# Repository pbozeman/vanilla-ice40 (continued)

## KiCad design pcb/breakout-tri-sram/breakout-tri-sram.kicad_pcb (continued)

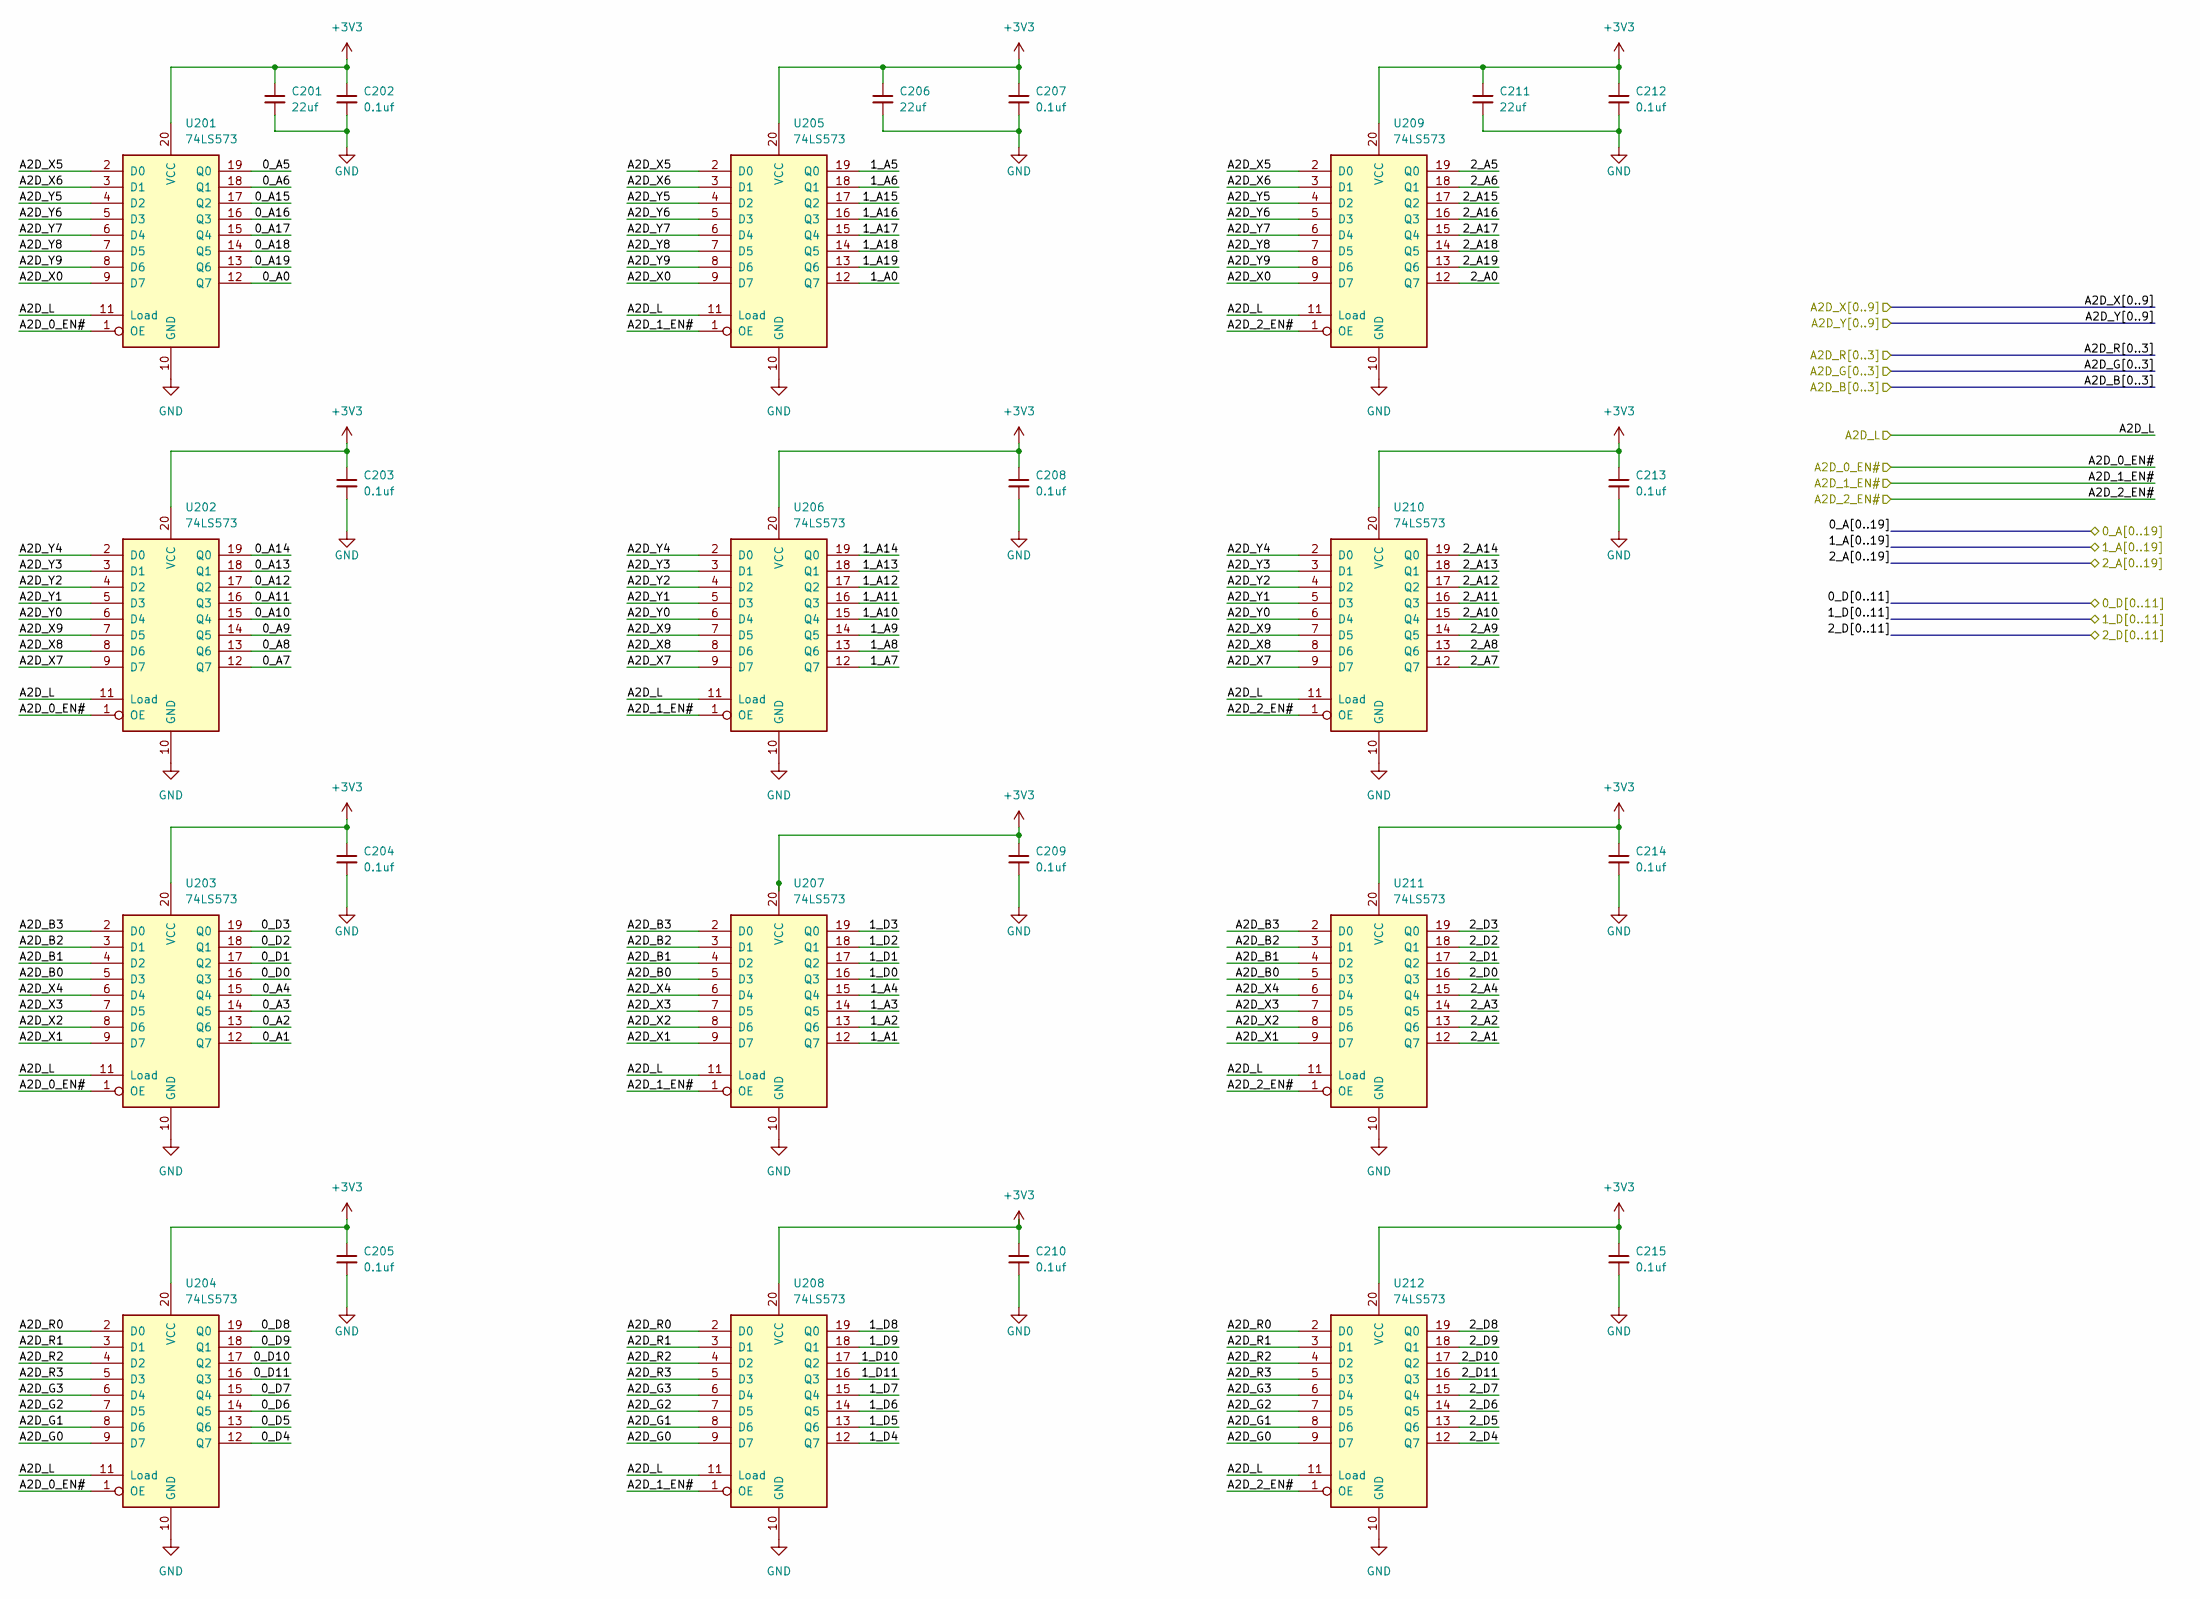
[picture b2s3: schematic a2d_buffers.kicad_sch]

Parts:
C201, C206, C211: 22uf; C_0603_1608Metric; LCSC Part # C59461
C202, C203, C204, C205, C207, C208, C209, C210, C212, C213, C214, C215: 0.1uf; C_0402_1005Metric; LCSC Part # C1525
U201, U202, U203, U204, U205, U206, U207, U208, U209, U210, U211, U212: 74LS573; SSOP-20_4.4x6.5mm_P0.65mm; LCSC Part # C7194124

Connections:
+3V3: C201.1, C202.1, C203.1, C204.1, C205.1, C206.1, C207.1, C208.1, C209.1, C210.1, C211.1, C212.1, C213.1, C214.1, C215.1, U201.20 (VCC), U202.20 (VCC), U203.20 (VCC), U204.20 (VCC), U205.20 (VCC), U206.20 (VCC), U207.20 (VCC), U208.20 (VCC), U209.20 (VCC), U210.20 (VCC), U211.20 (VCC), U212.20 (VCC); also elsewhere on the board
/0_A0: U201.12 (Q7); also elsewhere on the board
/0_A1: U203.12 (Q7); also elsewhere on the board
/0_A2: U203.13 (Q6); also elsewhere on the board
/0_A3: U203.14 (Q5); also elsewhere on the board
/0_A4: U203.15 (Q4); also elsewhere on the board
/0_A5: U201.19 (Q0); also elsewhere on the board
/0_A6: U201.18 (Q1); also elsewhere on the board
/0_A7: U202.12 (Q7); also elsewhere on the board
/0_A8: U202.13 (Q6); also elsewhere on the board
/0_A9: U202.14 (Q5); also elsewhere on the board
/0_A10: U202.15 (Q4); also elsewhere on the board
/0_A11: U202.16 (Q3); also elsewhere on the board
/0_A12: U202.17 (Q2); also elsewhere on the board
/0_A13: U202.18 (Q1); also elsewhere on the board
/0_A14: U202.19 (Q0); also elsewhere on the board
/0_A15: U201.17 (Q2); also elsewhere on the board
/0_A16: U201.16 (Q3); also elsewhere on the board
/0_A17: U201.15 (Q4); also elsewhere on the board
/0_A18: U201.14 (Q5); also elsewhere on the board
/0_A19: U201.13 (Q6); also elsewhere on the board
/0_D0: U203.16 (Q3); also elsewhere on the board
/0_D1: U203.17 (Q2); also elsewhere on the board
/0_D2: U203.18 (Q1); also elsewhere on the board
/0_D3: U203.19 (Q0); also elsewhere on the board
/0_D4: U204.12 (Q7); also elsewhere on the board
/0_D5: U204.13 (Q6); also elsewhere on the board
/0_D6: U204.14 (Q5); also elsewhere on the board
/0_D7: U204.15 (Q4); also elsewhere on the board
/0_D8: U204.19 (Q0); also elsewhere on the board
/0_D9: U204.18 (Q1); also elsewhere on the board
/0_D10: U204.17 (Q2); also elsewhere on the board
/0_D11: U204.16 (Q3); also elsewhere on the board
/1_A0: U205.12 (Q7); also elsewhere on the board
/1_A1: U207.12 (Q7); also elsewhere on the board
/1_A2: U207.13 (Q6); also elsewhere on the board
/1_A3: U207.14 (Q5); also elsewhere on the board
/1_A4: U207.15 (Q4); also elsewhere on the board
/1_A5: U205.19 (Q0); also elsewhere on the board
/1_A6: U205.18 (Q1); also elsewhere on the board
/1_A7: U206.12 (Q7); also elsewhere on the board
/1_A8: U206.13 (Q6); also elsewhere on the board
/1_A9: U206.14 (Q5); also elsewhere on the board
/1_A10: U206.15 (Q4); also elsewhere on the board
/1_A11: U206.16 (Q3); also elsewhere on the board
/1_A12: U206.17 (Q2); also elsewhere on the board
/1_A13: U206.18 (Q1); also elsewhere on the board
/1_A14: U206.19 (Q0); also elsewhere on the board
/1_A15: U205.17 (Q2); also elsewhere on the board
/1_A16: U205.16 (Q3); also elsewhere on the board
/1_A17: U205.15 (Q4); also elsewhere on the board
/1_A18: U205.14 (Q5); also elsewhere on the board
/1_A19: U205.13 (Q6); also elsewhere on the board
/1_D0: U207.16 (Q3); also elsewhere on the board
/1_D1: U207.17 (Q2); also elsewhere on the board
/1_D2: U207.18 (Q1); also elsewhere on the board
/1_D3: U207.19 (Q0); also elsewhere on the board
/1_D4: U208.12 (Q7); also elsewhere on the board
/1_D5: U208.13 (Q6); also elsewhere on the board
/1_D6: U208.14 (Q5); also elsewhere on the board
/1_D7: U208.15 (Q4); also elsewhere on the board
/1_D8: U208.19 (Q0); also elsewhere on the board
/1_D9: U208.18 (Q1); also elsewhere on the board
/1_D10: U208.17 (Q2); also elsewhere on the board
/1_D11: U208.16 (Q3); also elsewhere on the board
/2_A0: U209.12 (Q7); also elsewhere on the board
/2_A1: U211.12 (Q7); also elsewhere on the board
/2_A2: U211.13 (Q6); also elsewhere on the board
/2_A3: U211.14 (Q5); also elsewhere on the board
/2_A4: U211.15 (Q4); also elsewhere on the board
/2_A5: U209.19 (Q0); also elsewhere on the board
/2_A6: U209.18 (Q1); also elsewhere on the board
/2_A7: U210.12 (Q7); also elsewhere on the board
/2_A8: U210.13 (Q6); also elsewhere on the board
/2_A9: U210.14 (Q5); also elsewhere on the board
/2_A10: U210.15 (Q4); also elsewhere on the board
/2_A11: U210.16 (Q3); also elsewhere on the board
/2_A12: U210.17 (Q2); also elsewhere on the board
/2_A13: U210.18 (Q1); also elsewhere on the board
/2_A14: U210.19 (Q0); also elsewhere on the board
/2_A15: U209.17 (Q2); also elsewhere on the board
/2_A16: U209.16 (Q3); also elsewhere on the board
/2_A17: U209.15 (Q4); also elsewhere on the board
/2_A18: U209.14 (Q5); also elsewhere on the board
/2_A19: U209.13 (Q6); also elsewhere on the board
/2_D0: U211.16 (Q3); also elsewhere on the board
/2_D1: U211.17 (Q2); also elsewhere on the board
/2_D2: U211.18 (Q1); also elsewhere on the board
/2_D3: U211.19 (Q0); also elsewhere on the board
/2_D4: U212.12 (Q7); also elsewhere on the board
/2_D5: U212.13 (Q6); also elsewhere on the board
/2_D6: U212.14 (Q5); also elsewhere on the board
/2_D7: U212.15 (Q4); also elsewhere on the board
/2_D8: U212.19 (Q0); also elsewhere on the board
/2_D9: U212.18 (Q1); also elsewhere on the board
/2_D10: U212.17 (Q2); also elsewhere on the board
/2_D11: U212.16 (Q3); also elsewhere on the board
/A2D_0_EN#: U201.1 (OE), U202.1 (OE), U203.1 (OE), U204.1 (OE); also elsewhere on the board
/A2D_1_EN#: U205.1 (OE), U206.1 (OE), U207.1 (OE), U208.1 (OE); also elsewhere on the board
/A2D_2_EN#: U209.1 (OE), U210.1 (OE), U211.1 (OE), U212.1 (OE); also elsewhere on the board
/A2D_B0: U203.5 (D3), U207.5 (D3), U211.5 (D3); also elsewhere on the board
/A2D_B1: U203.4 (D2), U207.4 (D2), U211.4 (D2); also elsewhere on the board
/A2D_B2: U203.3 (D1), U207.3 (D1), U211.3 (D1); also elsewhere on the board
/A2D_B3: U203.2 (D0), U207.2 (D0), U211.2 (D0); also elsewhere on the board
/A2D_G0: U204.9 (D7), U208.9 (D7), U212.9 (D7); also elsewhere on the board
/A2D_G1: U204.8 (D6), U208.8 (D6), U212.8 (D6); also elsewhere on the board
/A2D_G2: U204.7 (D5), U208.7 (D5), U212.7 (D5); also elsewhere on the board
/A2D_G3: U204.6 (D4), U208.6 (D4), U212.6 (D4); also elsewhere on the board
/A2D_L: U201.11 (Load), U202.11 (Load), U203.11 (Load), U204.11 (Load), U205.11 (Load), U206.11 (Load), U207.11 (Load), U208.11 (Load), U209.11 (Load), U210.11 (Load), U211.11 (Load), U212.11 (Load); also elsewhere on the board
/A2D_R0: U204.2 (D0), U208.2 (D0), U212.2 (D0); also elsewhere on the board
/A2D_R1: U204.3 (D1), U208.3 (D1), U212.3 (D1); also elsewhere on the board
/A2D_R2: U204.4 (D2), U208.4 (D2), U212.4 (D2); also elsewhere on the board
/A2D_R3: U204.5 (D3), U208.5 (D3), U212.5 (D3); also elsewhere on the board
/A2D_X0: U201.9 (D7), U205.9 (D7), U209.9 (D7); also elsewhere on the board
/A2D_X1: U203.9 (D7), U207.9 (D7), U211.9 (D7); also elsewhere on the board
/A2D_X2: U203.8 (D6), U207.8 (D6), U211.8 (D6); also elsewhere on the board
/A2D_X3: U203.7 (D5), U207.7 (D5), U211.7 (D5); also elsewhere on the board
/A2D_X4: U203.6 (D4), U207.6 (D4), U211.6 (D4); also elsewhere on the board
/A2D_X5: U201.2 (D0), U205.2 (D0), U209.2 (D0); also elsewhere on the board
/A2D_X6: U201.3 (D1), U205.3 (D1), U209.3 (D1); also elsewhere on the board
/A2D_X7: U202.9 (D7), U206.9 (D7), U210.9 (D7); also elsewhere on the board
/A2D_X8: U202.8 (D6), U206.8 (D6), U210.8 (D6); also elsewhere on the board
/A2D_X9: U202.7 (D5), U206.7 (D5), U210.7 (D5); also elsewhere on the board
/A2D_Y0: U202.6 (D4), U206.6 (D4), U210.6 (D4); also elsewhere on the board
/A2D_Y1: U202.5 (D3), U206.5 (D3), U210.5 (D3); also elsewhere on the board
/A2D_Y2: U202.4 (D2), U206.4 (D2), U210.4 (D2); also elsewhere on the board
/A2D_Y3: U202.3 (D1), U206.3 (D1), U210.3 (D1); also elsewhere on the board
/A2D_Y4: U202.2 (D0), U206.2 (D0), U210.2 (D0); also elsewhere on the board
/A2D_Y5: U201.4 (D2), U205.4 (D2), U209.4 (D2); also elsewhere on the board
/A2D_Y6: U201.5 (D3), U205.5 (D3), U209.5 (D3); also elsewhere on the board
/A2D_Y7: U201.6 (D4), U205.6 (D4), U209.6 (D4); also elsewhere on the board
/A2D_Y8: U201.7 (D5), U205.7 (D5), U209.7 (D5); also elsewhere on the board
/A2D_Y9: U201.8 (D6), U205.8 (D6), U209.8 (D6); also elsewhere on the board
GND: C201.2, C202.2, C203.2, C204.2, C205.2, C206.2, C207.2, C208.2, C209.2, C210.2, C211.2, C212.2, C213.2, C214.2, C215.2, U201.10 (GND), U202.10 (GND), U203.10 (GND), U204.10 (GND), U205.10 (GND), U206.10 (GND), U207.10 (GND), U208.10 (GND), U209.10 (GND), U210.10 (GND), U211.10 (GND), U212.10 (GND); also elsewhere on the board

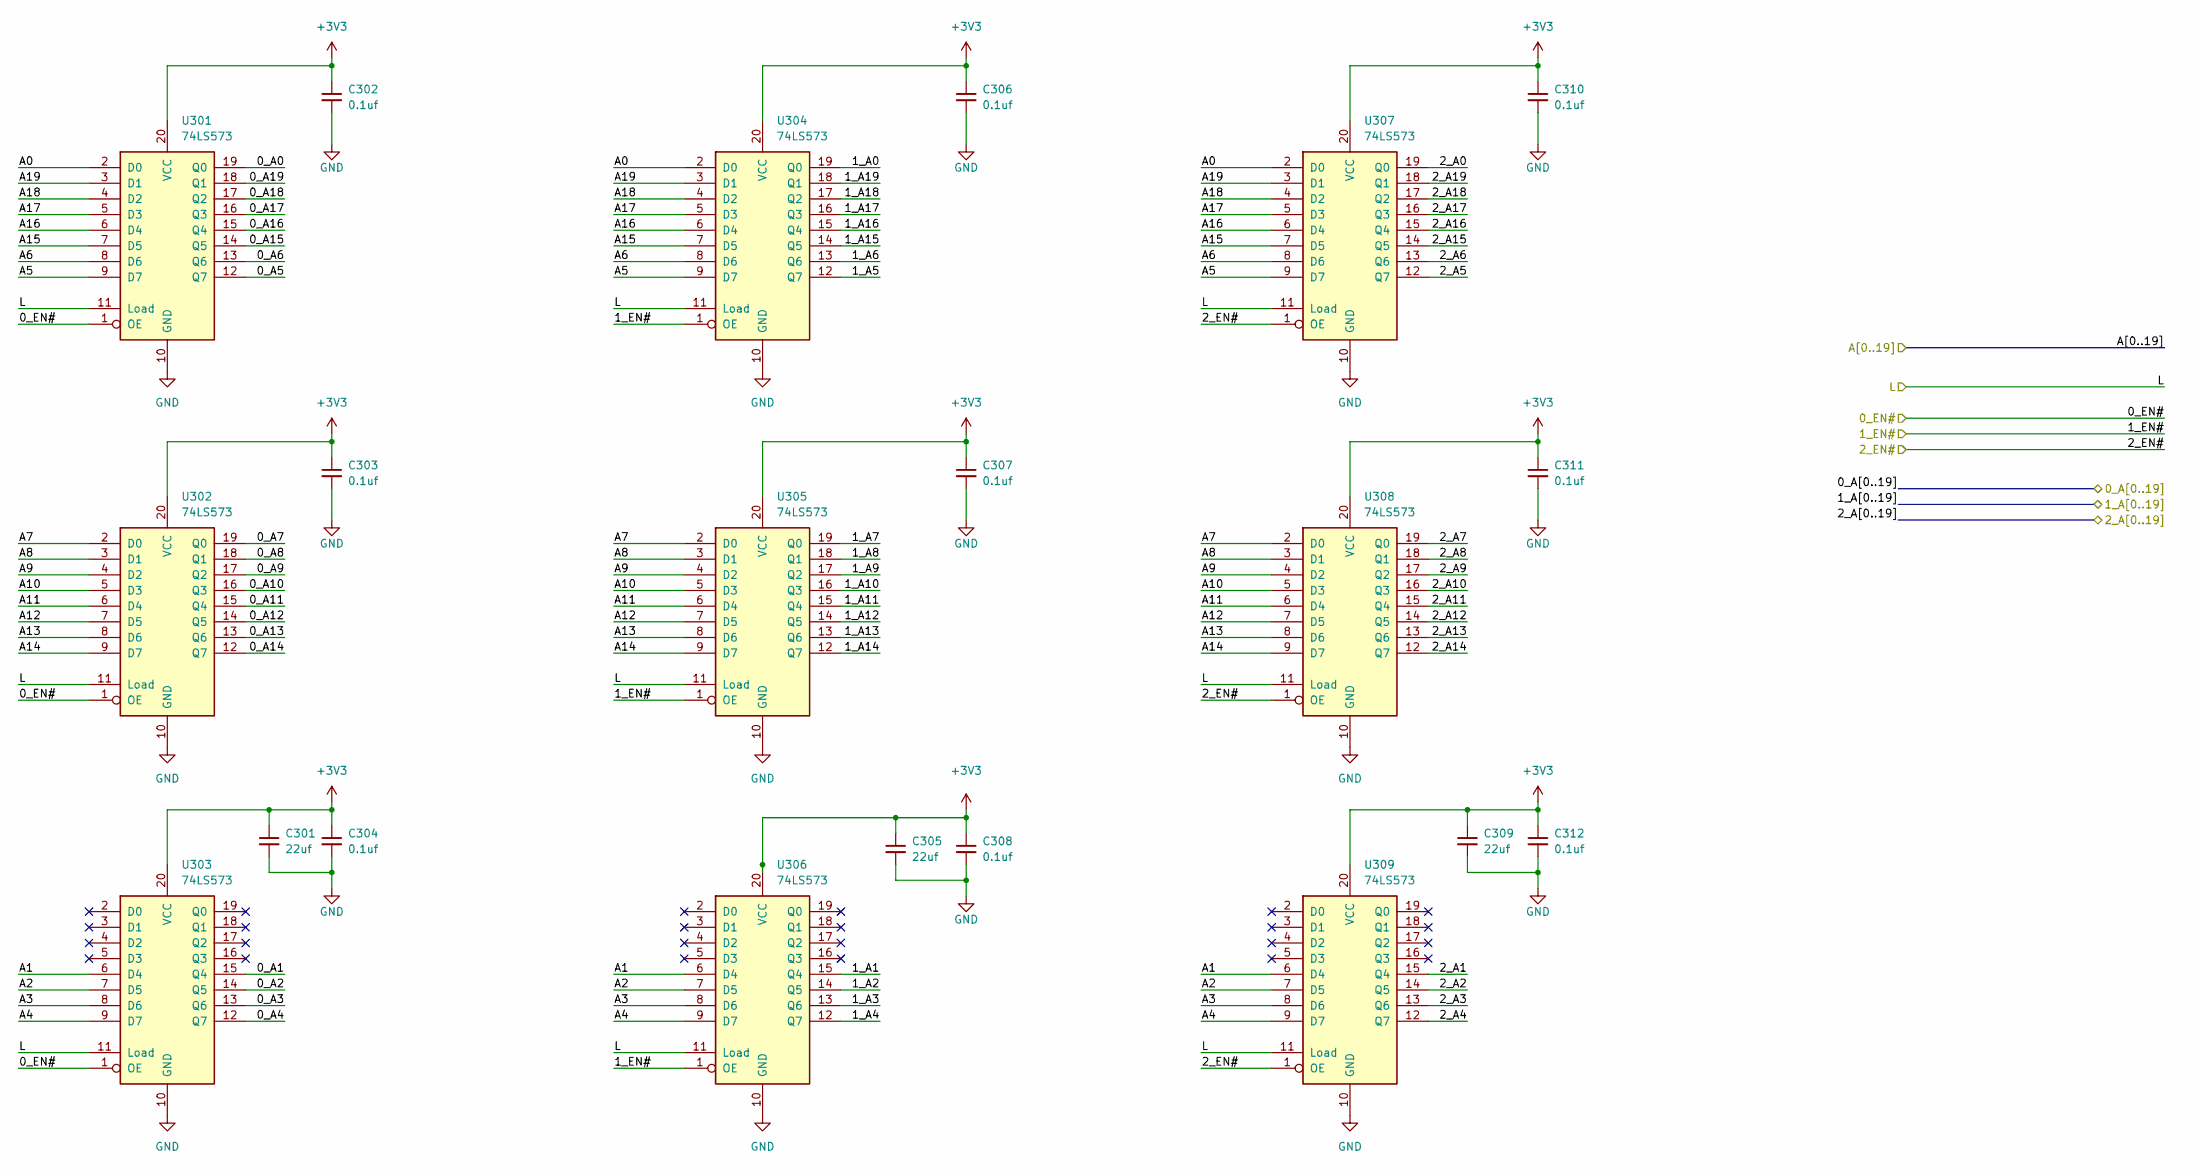
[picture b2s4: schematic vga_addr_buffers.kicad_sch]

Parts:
C301, C305, C309: 22uf; C_0603_1608Metric; LCSC Part # C59461
C302, C303, C304, C306, C307, C308, C310, C311, C312: 0.1uf; C_0402_1005Metric; LCSC Part # C1525
U301, U302, U303, U304, U305, U306, U307, U308, U309: 74LS573; SSOP-20_4.4x6.5mm_P0.65mm; LCSC Part # C7194124

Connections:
+3V3: C301.1, C302.1, C303.1, C304.1, C305.1, C306.1, C307.1, C308.1, C309.1, C310.1, C311.1, C312.1, U301.20 (VCC), U302.20 (VCC), U303.20 (VCC), U304.20 (VCC), U305.20 (VCC), U306.20 (VCC), U307.20 (VCC), U308.20 (VCC), U309.20 (VCC); also elsewhere on the board
/0_A0: U301.19 (Q0); also elsewhere on the board
/0_A1: U303.15 (Q4); also elsewhere on the board
/0_A2: U303.14 (Q5); also elsewhere on the board
/0_A3: U303.13 (Q6); also elsewhere on the board
/0_A4: U303.12 (Q7); also elsewhere on the board
/0_A5: U301.12 (Q7); also elsewhere on the board
/0_A6: U301.13 (Q6); also elsewhere on the board
/0_A7: U302.19 (Q0); also elsewhere on the board
/0_A8: U302.18 (Q1); also elsewhere on the board
/0_A9: U302.17 (Q2); also elsewhere on the board
/0_A10: U302.16 (Q3); also elsewhere on the board
/0_A11: U302.15 (Q4); also elsewhere on the board
/0_A12: U302.14 (Q5); also elsewhere on the board
/0_A13: U302.13 (Q6); also elsewhere on the board
/0_A14: U302.12 (Q7); also elsewhere on the board
/0_A15: U301.14 (Q5); also elsewhere on the board
/0_A16: U301.15 (Q4); also elsewhere on the board
/0_A17: U301.16 (Q3); also elsewhere on the board
/0_A18: U301.17 (Q2); also elsewhere on the board
/0_A19: U301.18 (Q1); also elsewhere on the board
/1_A0: U304.19 (Q0); also elsewhere on the board
/1_A1: U306.15 (Q4); also elsewhere on the board
/1_A2: U306.14 (Q5); also elsewhere on the board
/1_A3: U306.13 (Q6); also elsewhere on the board
/1_A4: U306.12 (Q7); also elsewhere on the board
/1_A5: U304.12 (Q7); also elsewhere on the board
/1_A6: U304.13 (Q6); also elsewhere on the board
/1_A7: U305.19 (Q0); also elsewhere on the board
/1_A8: U305.18 (Q1); also elsewhere on the board
/1_A9: U305.17 (Q2); also elsewhere on the board
/1_A10: U305.16 (Q3); also elsewhere on the board
/1_A11: U305.15 (Q4); also elsewhere on the board
/1_A12: U305.14 (Q5); also elsewhere on the board
/1_A13: U305.13 (Q6); also elsewhere on the board
/1_A14: U305.12 (Q7); also elsewhere on the board
/1_A15: U304.14 (Q5); also elsewhere on the board
/1_A16: U304.15 (Q4); also elsewhere on the board
/1_A17: U304.16 (Q3); also elsewhere on the board
/1_A18: U304.17 (Q2); also elsewhere on the board
/1_A19: U304.18 (Q1); also elsewhere on the board
/2_A0: U307.19 (Q0); also elsewhere on the board
/2_A1: U309.15 (Q4); also elsewhere on the board
/2_A2: U309.14 (Q5); also elsewhere on the board
/2_A3: U309.13 (Q6); also elsewhere on the board
/2_A4: U309.12 (Q7); also elsewhere on the board
/2_A5: U307.12 (Q7); also elsewhere on the board
/2_A6: U307.13 (Q6); also elsewhere on the board
/2_A7: U308.19 (Q0); also elsewhere on the board
/2_A8: U308.18 (Q1); also elsewhere on the board
/2_A9: U308.17 (Q2); also elsewhere on the board
/2_A10: U308.16 (Q3); also elsewhere on the board
/2_A11: U308.15 (Q4); also elsewhere on the board
/2_A12: U308.14 (Q5); also elsewhere on the board
/2_A13: U308.13 (Q6); also elsewhere on the board
/2_A14: U308.12 (Q7); also elsewhere on the board
/2_A15: U307.14 (Q5); also elsewhere on the board
/2_A16: U307.15 (Q4); also elsewhere on the board
/2_A17: U307.16 (Q3); also elsewhere on the board
/2_A18: U307.17 (Q2); also elsewhere on the board
/2_A19: U307.18 (Q1); also elsewhere on the board
/VGA_0_A_EN#: U301.1 (OE), U302.1 (OE), U303.1 (OE); also elsewhere on the board
/VGA_1_A_EN#: U304.1 (OE), U305.1 (OE), U306.1 (OE); also elsewhere on the board
/VGA_2_A_EN#: U307.1 (OE), U308.1 (OE), U309.1 (OE); also elsewhere on the board
/VGA_A0: U301.2 (D0), U304.2 (D0), U307.2 (D0); also elsewhere on the board
/VGA_A1: U303.6 (D4), U306.6 (D4), U309.6 (D4); also elsewhere on the board
/VGA_A2: U303.7 (D5), U306.7 (D5), U309.7 (D5); also elsewhere on the board
/VGA_A3: U303.8 (D6), U306.8 (D6), U309.8 (D6); also elsewhere on the board
/VGA_A4: U303.9 (D7), U306.9 (D7), U309.9 (D7); also elsewhere on the board
/VGA_A5: U301.9 (D7), U304.9 (D7), U307.9 (D7); also elsewhere on the board
/VGA_A6: U301.8 (D6), U304.8 (D6), U307.8 (D6); also elsewhere on the board
/VGA_A7: U302.2 (D0), U305.2 (D0), U308.2 (D0); also elsewhere on the board
/VGA_A8: U302.3 (D1), U305.3 (D1), U308.3 (D1); also elsewhere on the board
/VGA_A9: U302.4 (D2), U305.4 (D2), U308.4 (D2); also elsewhere on the board
/VGA_A10: U302.5 (D3), U305.5 (D3), U308.5 (D3); also elsewhere on the board
/VGA_A11: U302.6 (D4), U305.6 (D4), U308.6 (D4); also elsewhere on the board
/VGA_A12: U302.7 (D5), U305.7 (D5), U308.7 (D5); also elsewhere on the board
/VGA_A13: U302.8 (D6), U305.8 (D6), U308.8 (D6); also elsewhere on the board
/VGA_A14: U302.9 (D7), U305.9 (D7), U308.9 (D7); also elsewhere on the board
/VGA_A15: U301.7 (D5), U304.7 (D5), U307.7 (D5); also elsewhere on the board
/VGA_A16: U301.6 (D4), U304.6 (D4), U307.6 (D4); also elsewhere on the board
/VGA_A17: U301.5 (D3), U304.5 (D3), U307.5 (D3); also elsewhere on the board
/VGA_A18: U301.4 (D2), U304.4 (D2), U307.4 (D2); also elsewhere on the board
/VGA_A19: U301.3 (D1), U304.3 (D1), U307.3 (D1); also elsewhere on the board
/VGA_A_L: U301.11 (Load), U302.11 (Load), U303.11 (Load), U304.11 (Load), U305.11 (Load), U306.11 (Load), U307.11 (Load), U308.11 (Load), U309.11 (Load); also elsewhere on the board
GND: C301.2, C302.2, C303.2, C304.2, C305.2, C306.2, C307.2, C308.2, C309.2, C310.2, C311.2, C312.2, U301.10 (GND), U302.10 (GND), U303.10 (GND), U304.10 (GND), U305.10 (GND), U306.10 (GND), U307.10 (GND), U308.10 (GND), U309.10 (GND); also elsewhere on the board

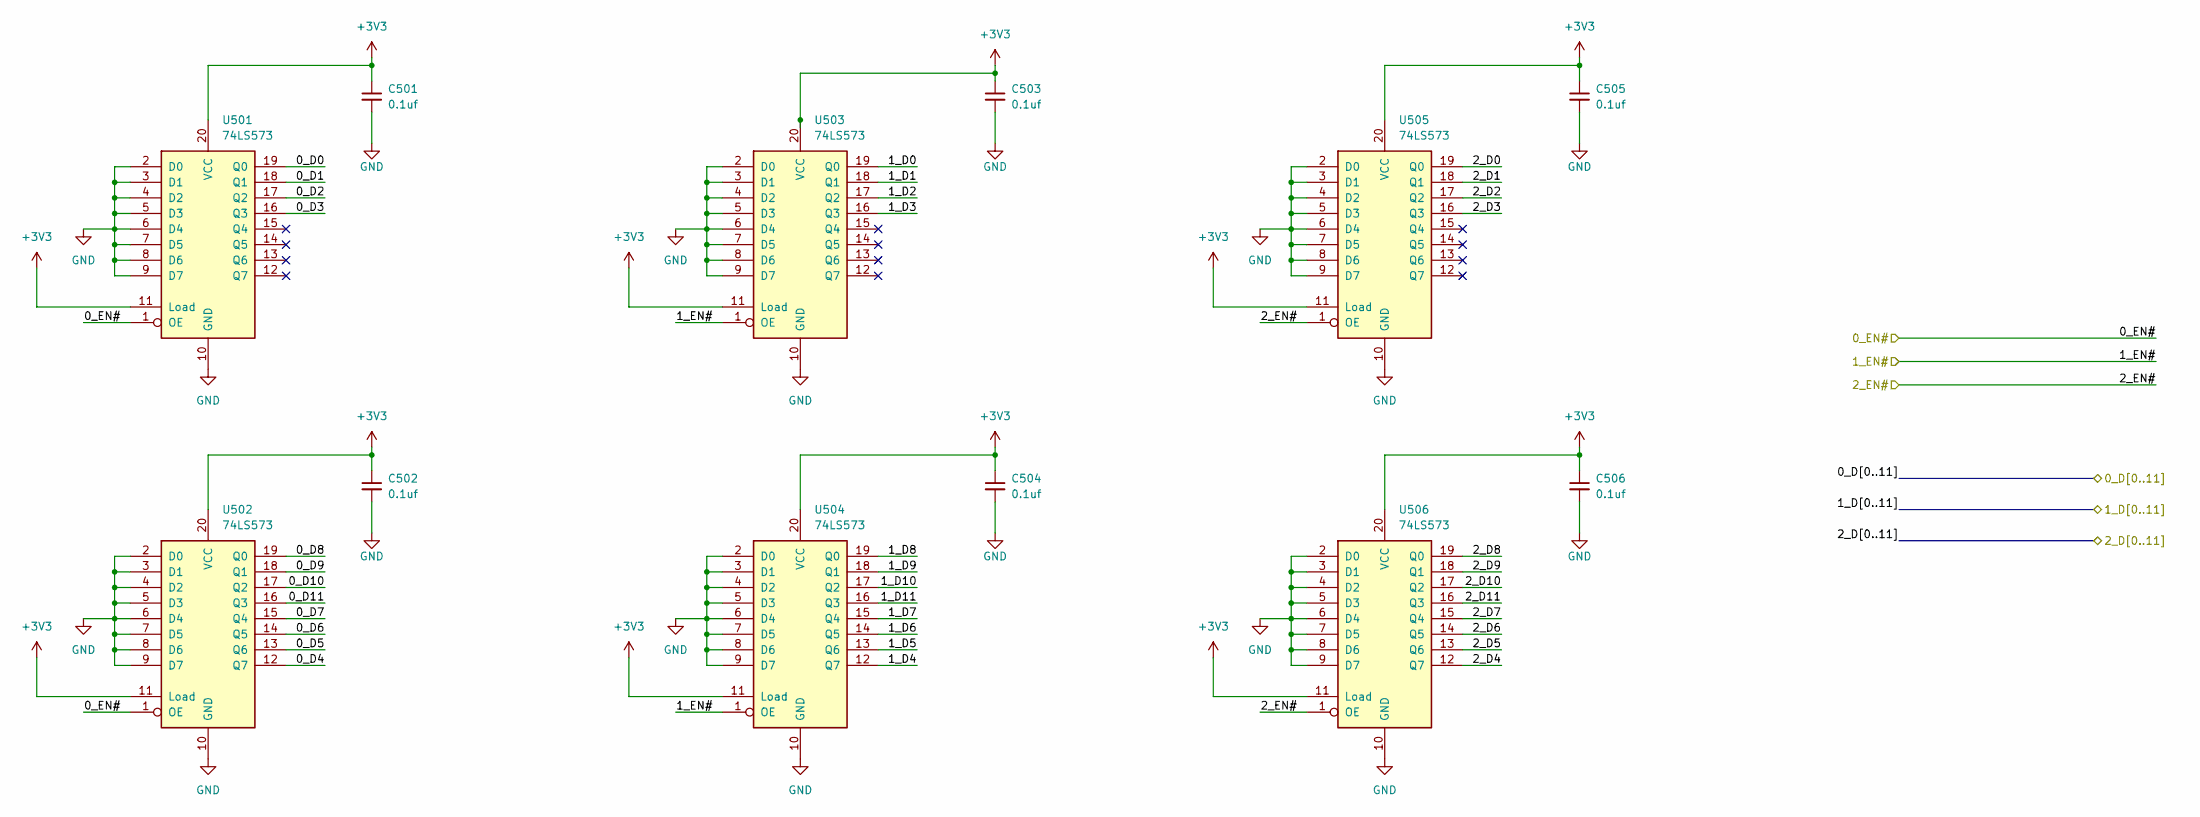
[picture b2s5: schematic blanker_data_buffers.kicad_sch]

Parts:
C501, C502, C503, C504, C505, C506: 0.1uf; C_0402_1005Metric; LCSC Part # C1525
U501, U502, U503, U504, U505, U506: 74LS573; SSOP-20_4.4x6.5mm_P0.65mm; LCSC Part # C7194124

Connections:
+3V3: C501.1, C502.1, C503.1, C504.1, C505.1, C506.1, U501.11 (Load), U501.20 (VCC), U502.11 (Load), U502.20 (VCC), U503.11 (Load), U503.20 (VCC), U504.11 (Load), U504.20 (VCC), U505.11 (Load), U505.20 (VCC), U506.11 (Load), U506.20 (VCC); also elsewhere on the board
/0_D0: U501.19 (Q0); also elsewhere on the board
/0_D1: U501.18 (Q1); also elsewhere on the board
/0_D2: U501.17 (Q2); also elsewhere on the board
/0_D3: U501.16 (Q3); also elsewhere on the board
/0_D4: U502.12 (Q7); also elsewhere on the board
/0_D5: U502.13 (Q6); also elsewhere on the board
/0_D6: U502.14 (Q5); also elsewhere on the board
/0_D7: U502.15 (Q4); also elsewhere on the board
/0_D8: U502.19 (Q0); also elsewhere on the board
/0_D9: U502.18 (Q1); also elsewhere on the board
/0_D10: U502.17 (Q2); also elsewhere on the board
/0_D11: U502.16 (Q3); also elsewhere on the board
/1_D0: U503.19 (Q0); also elsewhere on the board
/1_D1: U503.18 (Q1); also elsewhere on the board
/1_D2: U503.17 (Q2); also elsewhere on the board
/1_D3: U503.16 (Q3); also elsewhere on the board
/1_D4: U504.12 (Q7); also elsewhere on the board
/1_D5: U504.13 (Q6); also elsewhere on the board
/1_D6: U504.14 (Q5); also elsewhere on the board
/1_D7: U504.15 (Q4); also elsewhere on the board
/1_D8: U504.19 (Q0); also elsewhere on the board
/1_D9: U504.18 (Q1); also elsewhere on the board
/1_D10: U504.17 (Q2); also elsewhere on the board
/1_D11: U504.16 (Q3); also elsewhere on the board
/2_D0: U505.19 (Q0); also elsewhere on the board
/2_D1: U505.18 (Q1); also elsewhere on the board
/2_D2: U505.17 (Q2); also elsewhere on the board
/2_D3: U505.16 (Q3); also elsewhere on the board
/2_D4: U506.12 (Q7); also elsewhere on the board
/2_D5: U506.13 (Q6); also elsewhere on the board
/2_D6: U506.14 (Q5); also elsewhere on the board
/2_D7: U506.15 (Q4); also elsewhere on the board
/2_D8: U506.19 (Q0); also elsewhere on the board
/2_D9: U506.18 (Q1); also elsewhere on the board
/2_D10: U506.17 (Q2); also elsewhere on the board
/2_D11: U506.16 (Q3); also elsewhere on the board
/BLK_0_EN#: U501.1 (OE), U502.1 (OE); also elsewhere on the board
/BLK_1_EN#: U503.1 (OE), U504.1 (OE); also elsewhere on the board
/BLK_2_EN#: U505.1 (OE), U506.1 (OE); also elsewhere on the board
GND: C501.2, C502.2, C503.2, C504.2, C505.2, C506.2, U501.2 (D0), U501.3 (D1), U501.4 (D2), U501.5 (D3), U501.6 (D4), U501.7 (D5), U501.8 (D6), U501.9 (D7), U501.10 (GND), U502.2 (D0), U502.3 (D1), U502.4 (D2), U502.5 (D3), U502.6 (D4), U502.7 (D5), U502.8 (D6), U502.9 (D7), U502.10 (GND), U503.2 (D0), U503.3 (D1), U503.4 (D2), U503.5 (D3), U503.6 (D4), U503.7 (D5), U503.8 (D6), U503.9 (D7), U503.10 (GND), U504.2 (D0), U504.3 (D1), U504.4 (D2), U504.5 (D3), U504.6 (D4), U504.7 (D5), U504.8 (D6), U504.9 (D7), U504.10 (GND), U505.2 (D0), U505.3 (D1), U505.4 (D2), U505.5 (D3), U505.6 (D4), U505.7 (D5), U505.8 (D6), U505.9 (D7), U505.10 (GND), U506.2 (D0), U506.3 (D1), U506.4 (D2), U506.5 (D3), U506.6 (D4), U506.7 (D5), U506.8 (D6), U506.9 (D7), U506.10 (GND); also elsewhere on the board

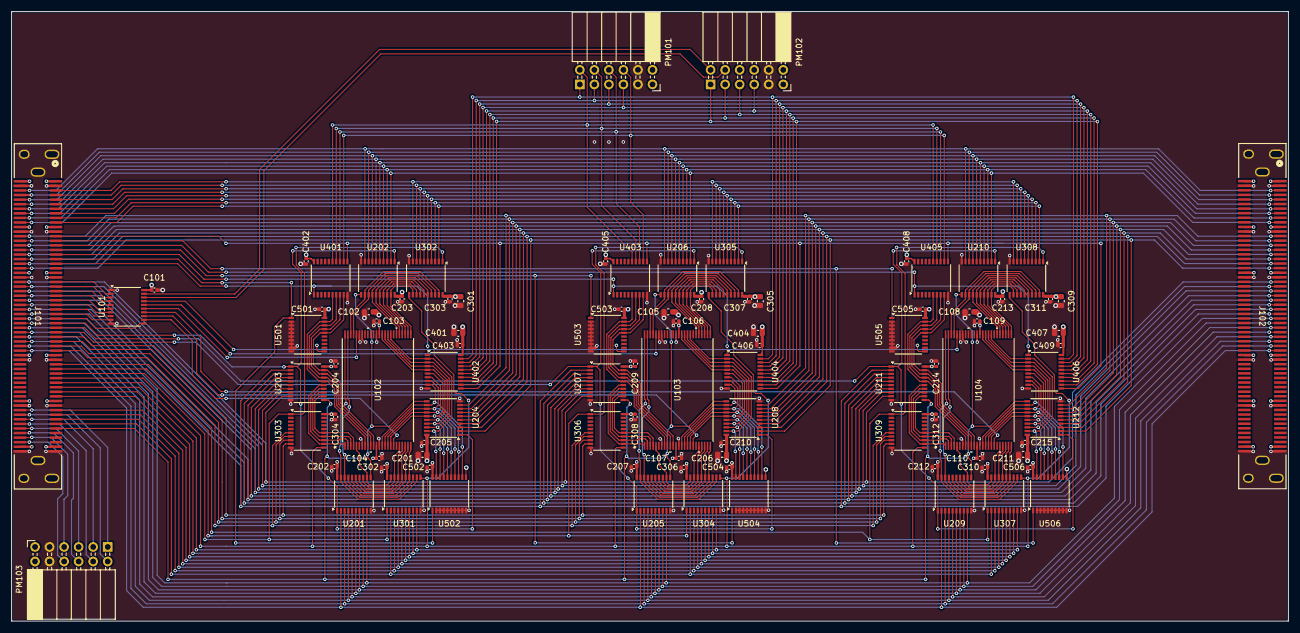
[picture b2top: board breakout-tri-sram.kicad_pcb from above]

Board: 4 copper layers, 223.2 x 106.5 mm, 94 parts (0 on the bottom side), 202 nets.
